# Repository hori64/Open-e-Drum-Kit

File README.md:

# Open-e-Drum-Kit

My Hello Drum based drum kit.

Pictures: https://photos.app.goo.gl/zvTpE33wYrmLLrem9

(Under construction...)

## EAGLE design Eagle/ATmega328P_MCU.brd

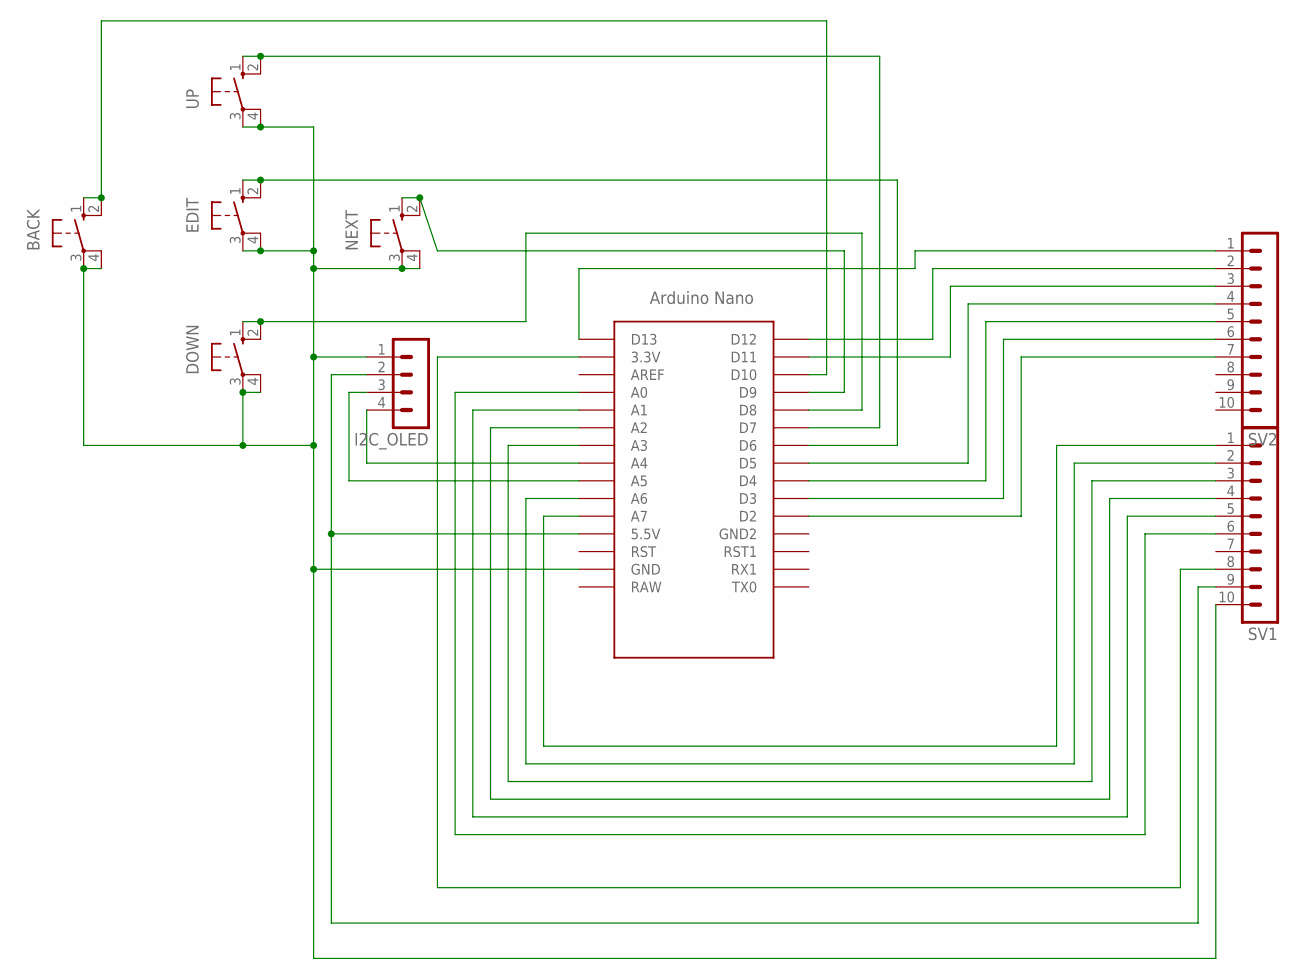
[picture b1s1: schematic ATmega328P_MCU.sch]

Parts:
ARDUINO: NANO
BACK: 10-XX; B3F-10XX
DOWN: 10-XX; B3F-10XX
EDIT: 10-XX; B3F-10XX
I2C_OLED: MA04-1
NEXT: 10-XX; B3F-10XX
SV1, SV2: MA10-1
UP: 10-XX; B3F-10XX

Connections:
unnamed: ARDUINO.D8, DOWN.1 (S), DOWN.2 (S1)
unnamed: ARDUINO.5V (5.5V), I2C_OLED.2, SV1.9
unnamed: ARDUINO.A4, I2C_OLED.4
unnamed: ARDUINO.A5, I2C_OLED.3
unnamed: ARDUINO.D5, SV2.4
unnamed: ARDUINO.D9, NEXT.1 (S), NEXT.2 (S1)
unnamed: ARDUINO.D7, UP.1 (S), UP.2 (S1)
unnamed: ARDUINO.D10, BACK.1 (S), BACK.2 (S1)
unnamed: ARDUINO.D6, EDIT.1 (S), EDIT.2 (S1)
unnamed: ARDUINO.D4, SV2.5
unnamed: ARDUINO.GND, BACK.3, BACK.4 (P1), DOWN.3, DOWN.4 (P1), EDIT.3, EDIT.4 (P1), I2C_OLED.1, NEXT.3, NEXT.4 (P1), SV1.10, UP.3, UP.4 (P1)
unnamed: ARDUINO.D3, SV2.6
unnamed: ARDUINO.D12, SV2.2
unnamed: ARDUINO.D11, SV2.3
unnamed: ARDUINO.3.3V, SV1.8
unnamed: ARDUINO.D13, SV2.1
unnamed: ARDUINO.A0, SV1.6
unnamed: ARDUINO.D2, SV2.7
unnamed: ARDUINO.A1, SV1.5
unnamed: ARDUINO.A2, SV1.4
unnamed: ARDUINO.A3, SV1.3
unnamed: ARDUINO.A6, SV1.2
unnamed: ARDUINO.A7, SV1.1

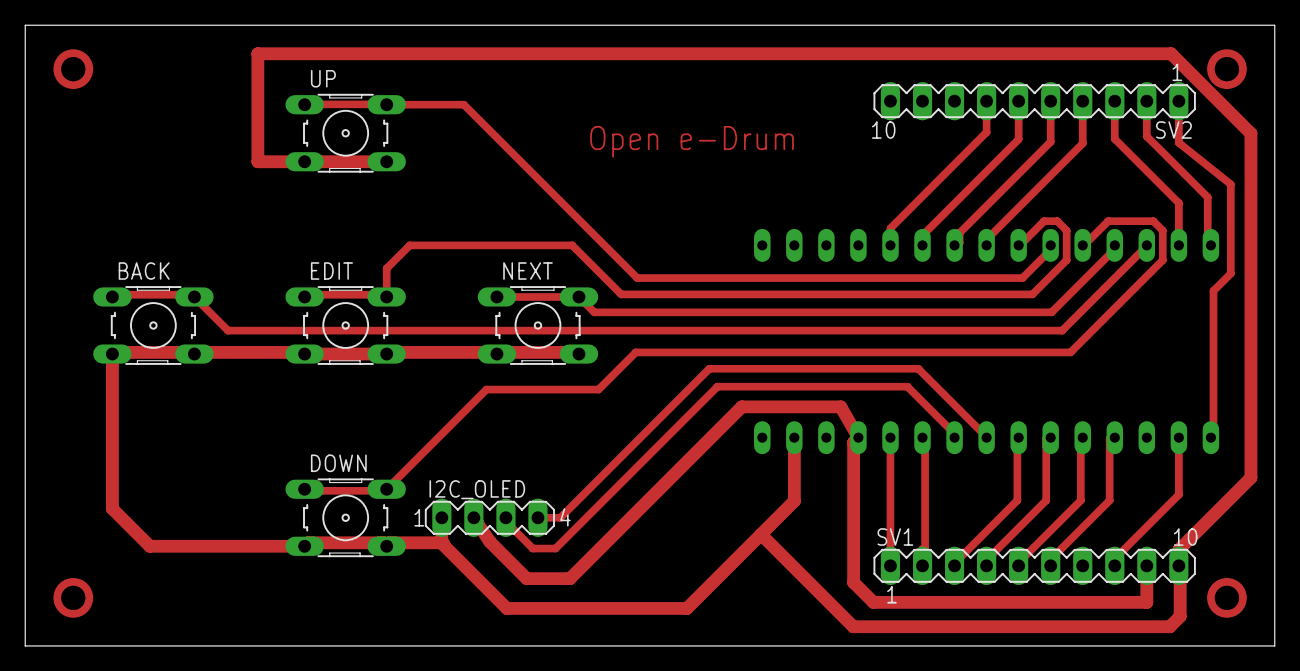
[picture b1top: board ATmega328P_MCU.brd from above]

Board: 2 copper layers, 99.0 x 49.2 mm, 9 parts (1 on the bottom side), 23 nets.

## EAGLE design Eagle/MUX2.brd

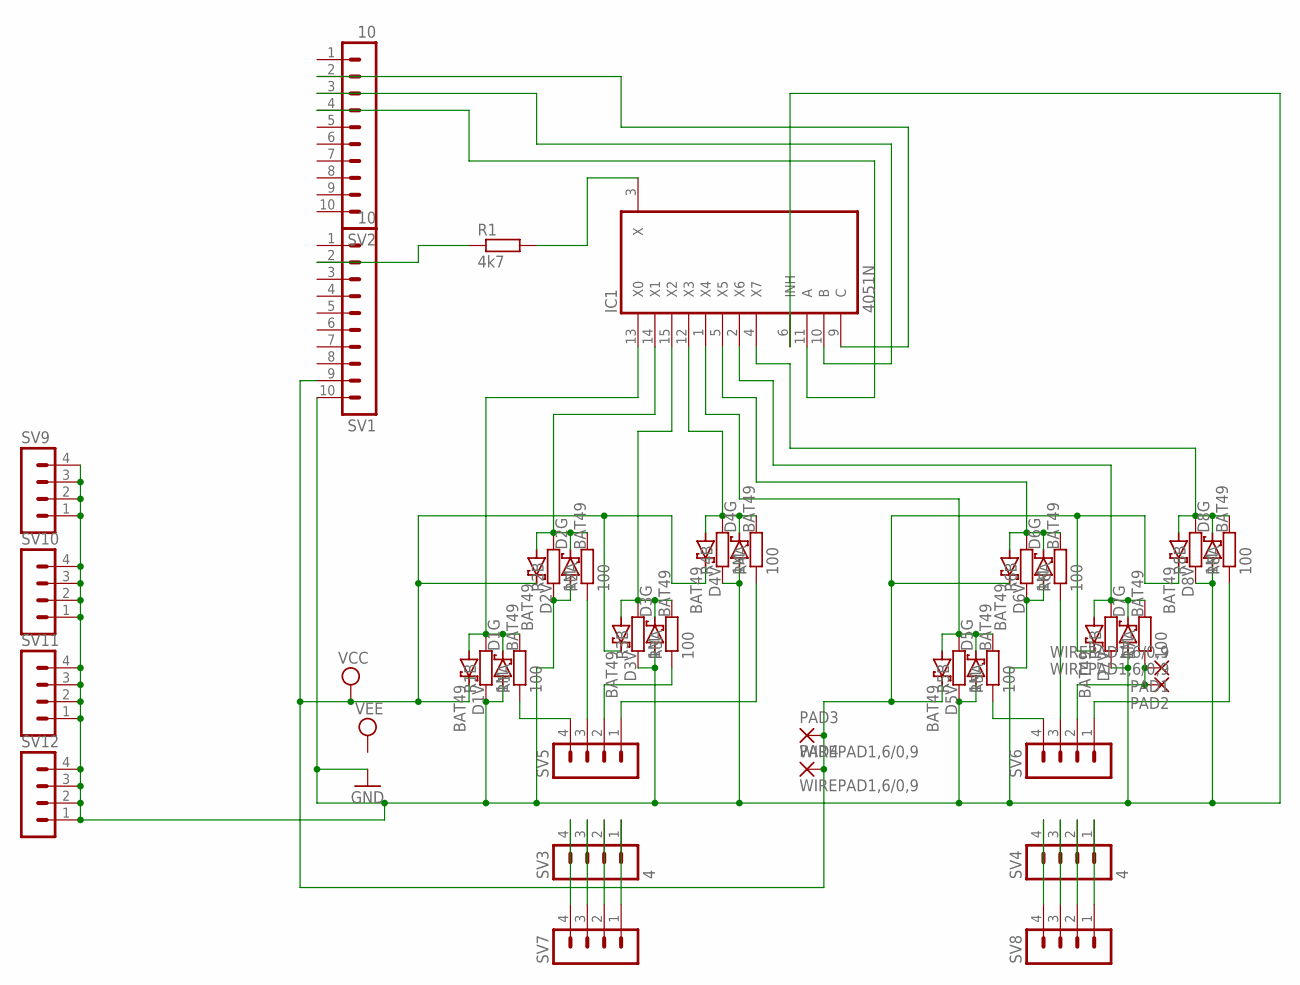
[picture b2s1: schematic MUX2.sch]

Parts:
D1G, D1V, D2G, D2V, D3G, D3V, D4G, D4V, D5G, D5V, D6G, D6V, D7G, D7V, D8G, D8V: BAT49; DO41-10
IC1: 4051N; DIL16
PAD1, PAD2, PAD3, PAD4: WIREPAD1,6/0,9; 1,6/0,9
R1: 4k7; 0204/7
R1A, R2A, R3A, R4A, R5A, R6A, R7A, R8A: 100; 0204/7
R1B, R2B, R3B, R4B, R5B, R6B, R7B, R8B: 1M; 0204/7
SV1, SV2: 10; MA10-1
SV3, SV4: 4; MA04-1
SV5, SV6, SV7, SV8, SV9, SV10, SV11, SV12: MA04-1

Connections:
GND: D1G.A, D2G.A, D3G.A, D4G.A, D5G.A, D6G.A, D7G.A, D8G.A, IC1.6 (INH), IC1.8 (GND), R1B.1, R2B.1, R3B.1, R4B.1, R5B.1, R6B.1, R7B.1, R8B.1, SV1.10, SV9.1, SV9.2, SV9.3, SV9.4, SV10.1, SV10.2, SV10.3, SV10.4, SV11.1, SV11.2, SV11.3, SV11.4, SV12.1, SV12.2, SV12.3, SV12.4
unnamed: R1A.1, SV5.4
unnamed: R1.1, SV1.2
unnamed: R2A.1, SV5.3
unnamed: R3A.1, SV5.2
unnamed: R5A.1, SV6.4
unnamed: D2G.C, D2V.A, IC1.14 (X1), R2A.2, R2B.2
unnamed: D1G.C, D1V.A, IC1.13 (X0), R1A.2, R1B.2
unnamed: R4A.1, SV5.1
unnamed: D5G.C, D5V.A, IC1.1 (X4), R5A.2, R5B.2
unnamed: IC1.9 (C), SV2.2
unnamed: D6G.C, D6V.A, IC1.5 (X5), R6A.2, R6B.2
unnamed: IC1.10 (B), SV2.3
unnamed: R6A.1, SV6.3
unnamed: D8G.C, D8V.A, IC1.4 (X7), R8A.2, R8B.2
unnamed: PAD1.1, PAD2.1, R7A.1, SV6.2
unnamed: R8A.1, SV6.1
unnamed: D7G.C, D7V.A, IC1.2 (X6), R7A.2, R7B.2
unnamed: SV3.4, SV7.4
unnamed: IC1.11 (A), SV2.4
unnamed: SV3.3, SV7.3
unnamed: SV3.2, SV7.2
unnamed: SV3.1, SV7.1
unnamed: SV4.4, SV8.4
unnamed: IC1.3 (X), R1.2
unnamed: SV4.3, SV8.3
unnamed: D4G.C, D4V.A, IC1.12 (X3), R4A.2, R4B.2
unnamed: SV4.2, SV8.2
unnamed: SV4.1, SV8.1
unnamed: D3G.C, D3V.A, IC1.15 (X2), R3A.2, R3B.2
VCC: D1V.C, D2V.C, D3V.C, D4V.C, D5V.C, D6V.C, D7V.C, D8V.C, IC1.16 (VCC), PAD3.1, PAD4.1, SV1.9
VEE: IC1.7 (VEE)

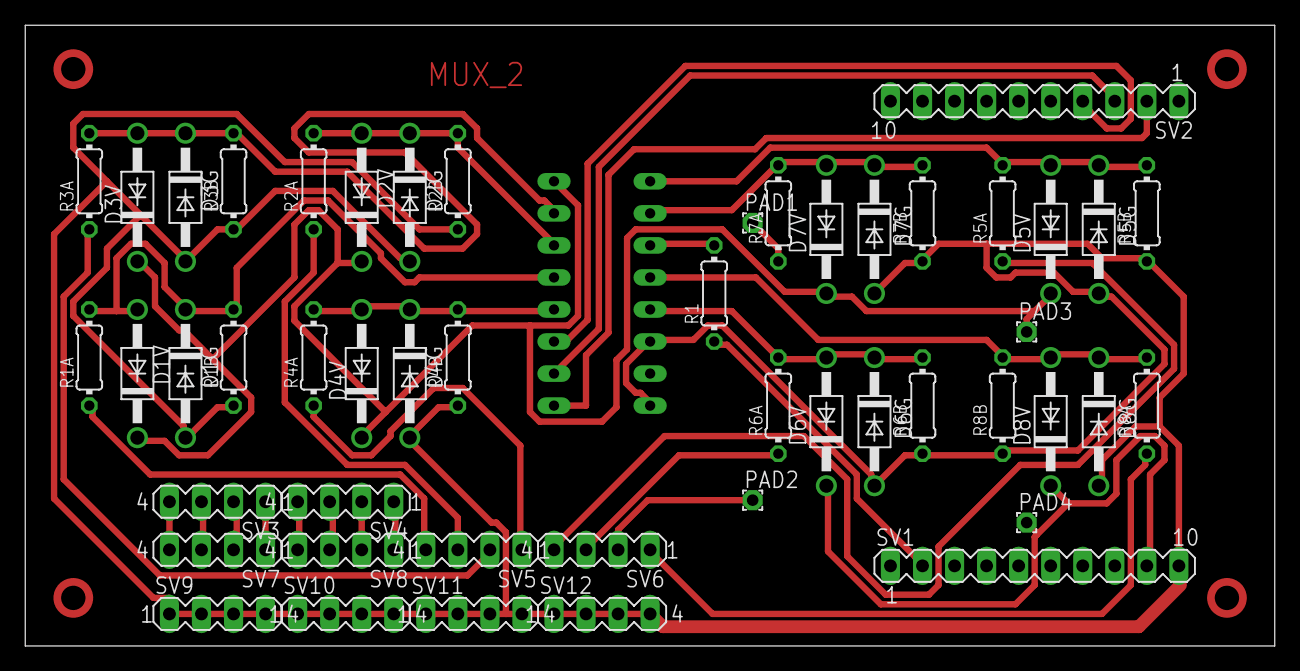
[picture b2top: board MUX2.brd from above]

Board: 2 copper layers, 99.0 x 49.2 mm, 50 parts (1 on the bottom side), 31 nets.

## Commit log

2020-01-31 Upload
2020-01-31 Eagle upload
2020-02-06 changing filenames and organizing
